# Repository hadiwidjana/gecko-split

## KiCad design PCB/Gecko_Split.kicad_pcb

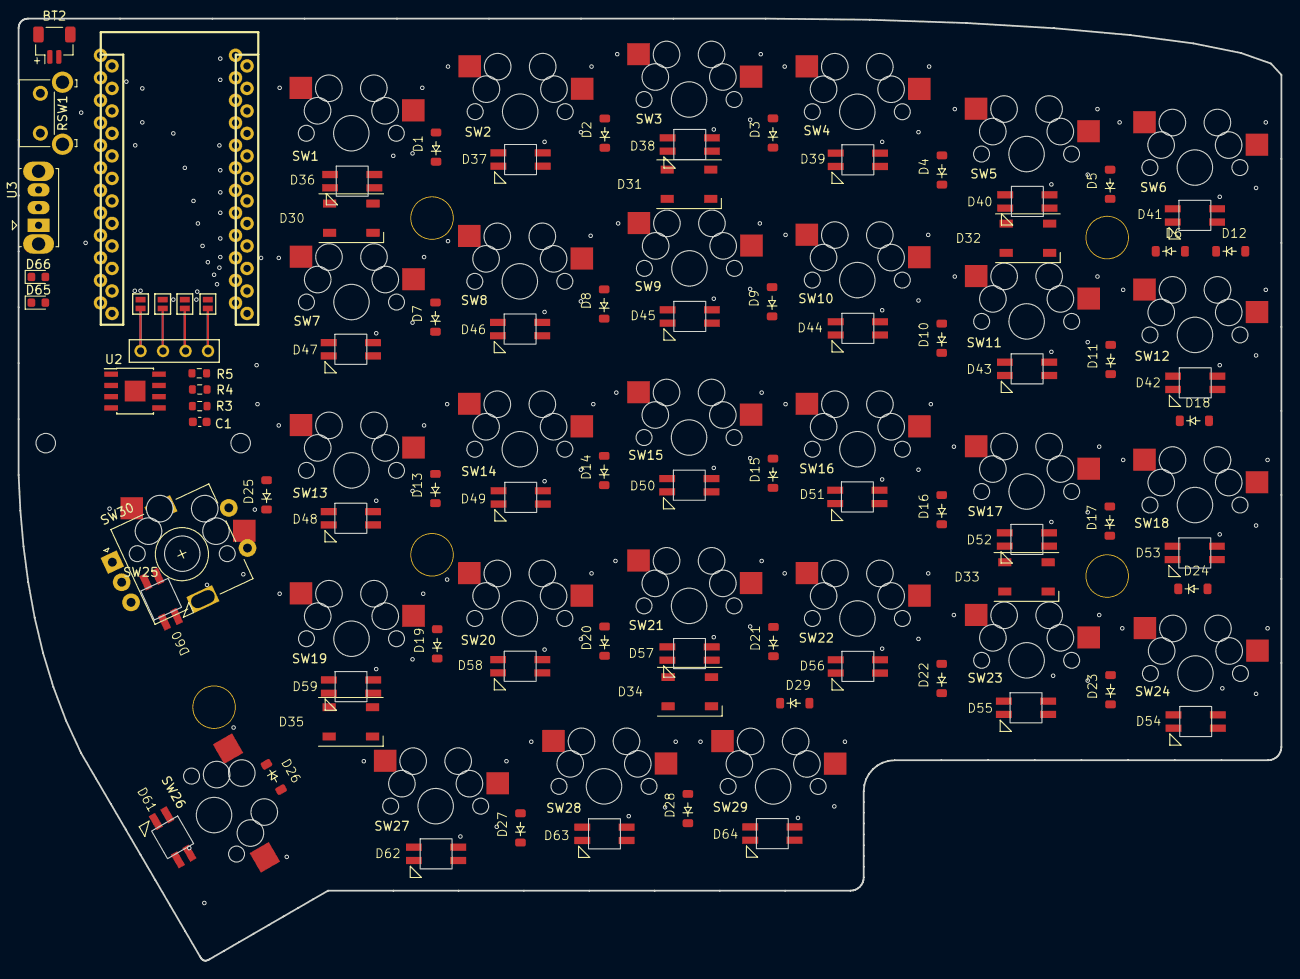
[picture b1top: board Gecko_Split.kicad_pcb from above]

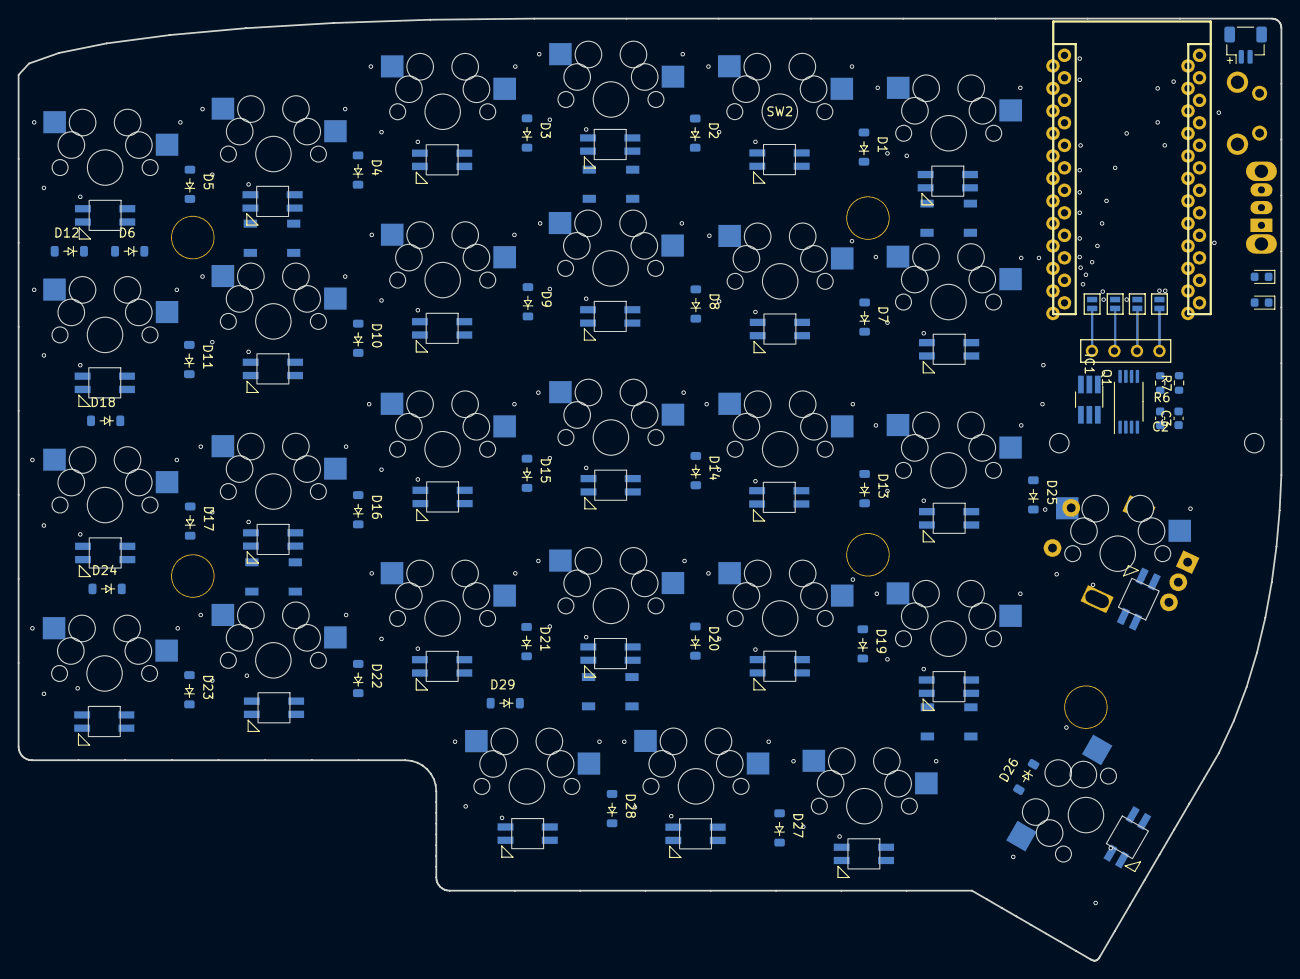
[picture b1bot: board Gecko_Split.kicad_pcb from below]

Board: 2 copper layers, 142.5 x 106.3 mm, 127 parts (10 on the bottom side), 98 nets.

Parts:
BT2: Battery_Cell; JST_SH_BM02B-SRSS-TB_1x02-1MP_P1.00mm_Vertical
C1, C2: 0.1UF-25V-5%; C_0603_1608Metric
C3: 10UF; C_0603_1608Metric
D1, D2, D3, D4, D5, D6, D7, D8, D9, D10, D11, D12, D13, D14, D15, D16, D17, D18, D19, D20, D21, D22, D23, D24, D25, D26, D27, D28, D29: D; D_SOD-123-BothSides
D30, D31, D32, D33, D34, D35: WS2812B; LED_WS2812B_BothSides
D36, D37, D38, D39, D40, D41, D42, D43, D44, D45, D46, D47, D48, D49, D50, D51, D52, D53, D54, D55, D56, D57, D58, D59, D60, D61, D62, D63, D64: SK6812MINI; LED_SK6812MINI_THROUGH
D65, D66: LED; LED_0603_1608Metric
IC1: DW01A; TSOT-23-6_HandSoldering
J2: OLED; OLED_4Pin
JP1, JP2, JP3, JP4, JP5, JP6, JP7, JP8: Jumper_NO_Small; Jumper
Q1: FS8205A; TSSOP-8_4.4x3mm_P0.65mm
R3, R4, R7: 1K OHM; R_0603_1608Metric
R5: 1.2K Ohm; R_0603_1608Metric
R6: 100 OHM; R_0603_1608Metric
RSW1: SW_RST; SW_SPST_Omron_B3F-315x_Angled
SW1, SW2, SW3, SW4, SW5, SW6, SW7, SW8, SW9, SW10, SW11, SW12, SW13, SW14, SW15, SW16, SW17, SW18, SW19, SW20, SW21, SW22, SW23, SW24, SW25, SW26, SW27, SW28, SW29: SW_PUSH; MX_Socket_18mm
SW30: RotaryEncoder_Switch; RotaryEncoder_Alps_EC11E-Switch_Vertical_H20mm
TH1, TH2: HOLE; HOLE_M2
TH3, TH4, TH5, TH6, TH7: HOLE; HOLE_M2_TH
U1: ProMicro; ProMicro_rev2
U2: TP4056; TP4056_SOIC-8
U3: SK12D07VG4; SW_Slide_1P2T_CK_OS102011MS2Q

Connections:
BAT+: C3.1, R6.1, U1.24 (RAW), U2.5 (BAT), U3.1
BAT-: C2.2, IC1.6 (GND), Q1.6, Q1.7
GND: BT2.2 (-), C1.2, C3.2, D30.3 (VSS), D31.3 (VSS), D32.3 (VSS), D33.3 (VSS), D34.3 (VSS), D35.3 (VSS), D36.2 (VSS), D37.2 (VSS), D38.2 (VSS), D39.2 (VSS), D40.2 (VSS), D41.2 (VSS), D42.2 (VSS), D43.2 (VSS), D44.2 (VSS), D45.2 (VSS), D46.2 (VSS), D47.2 (VSS), D48.2 (VSS), D49.2 (VSS), D50.2 (VSS), D51.2 (VSS), D52.2 (VSS), D53.2 (VSS), D54.2 (VSS), D55.2 (VSS), D56.2 (VSS), D57.2 (VSS), D58.2 (VSS), D59.2 (VSS), D60.2 (VSS), D61.2 (VSS), D62.2 (VSS), D63.2 (VSS), D64.2 (VSS), JP1.2, JP8.2, Q1.2, Q1.3, R5.2, R7.2, RSW1.1, SW30.C, U1.3 (GND), U1.4 (GND), U1.23 (GND), U2.1 (TEMP), U2.3 (GND)
LED: D30.4 (DIN), U1.1 (TX(PD3))
unnamed: BT2.1 (+), U3.3
unnamed: D1.2 (A), SW1.2
unnamed: D2.2 (A), SW2.2
unnamed: D3.2 (A), SW3.2
unnamed: D4.2 (A), SW4.2
unnamed: D5.2 (A), SW5.2
unnamed: D6.2 (A), SW6.2
unnamed: D7.2 (A), SW7.2
unnamed: D8.2 (A), SW8.2
unnamed: D9.2 (A), SW9.2
unnamed: D10.2 (A), SW10.2
unnamed: D11.2 (A), SW11.2
unnamed: D12.2 (A), SW12.2
unnamed: D13.2 (A), SW13.2
unnamed: D14.2 (A), SW14.2
unnamed: D15.2 (A), SW15.2
unnamed: D16.2 (A), SW16.2
unnamed: D17.2 (A), SW17.2
unnamed: D18.2 (A), SW18.2
unnamed: D19.2 (A), SW19.2
unnamed: D20.2 (A), SW20.2
unnamed: D21.2 (A), SW21.2
unnamed: D22.2 (A), SW22.2
unnamed: D23.2 (A), SW23.2
unnamed: D24.2 (A), SW24.2
unnamed: D25.2 (A), SW25.2, SW30.S2
unnamed: D26.2 (A), SW26.2
unnamed: D27.2 (A), SW27.2
unnamed: D28.2 (A), SW28.2
unnamed: D29.2 (A), SW29.2
unnamed: D30.2 (DOUT), D31.4 (DIN)
unnamed: D31.2 (DOUT), D32.4 (DIN)
unnamed: D32.2 (DOUT), D33.4 (DIN)
unnamed: D33.2 (DOUT), D34.4 (DIN)
unnamed: D34.2 (DOUT), D35.4 (DIN)
unnamed: D35.2 (DOUT), D36.3 (DIN)
unnamed: D36.1 (DOUT), D37.3 (DIN)
unnamed: D37.1 (DOUT), D38.3 (DIN)
unnamed: D38.1 (DOUT), D39.3 (DIN)
unnamed: D39.1 (DOUT), D40.3 (DIN)
unnamed: D40.1 (DOUT), D41.3 (DIN)
unnamed: D41.1 (DOUT), D42.3 (DIN)
unnamed: D42.1 (DOUT), D43.3 (DIN)
unnamed: D43.1 (DOUT), D44.3 (DIN)
unnamed: D44.1 (DOUT), D45.3 (DIN)
unnamed: D45.1 (DOUT), D46.3 (DIN)
unnamed: D46.1 (DOUT), D47.3 (DIN)
unnamed: D47.1 (DOUT), D48.3 (DIN)
unnamed: D48.1 (DOUT), D49.3 (DIN)
unnamed: D49.1 (DOUT), D50.3 (DIN)
unnamed: D50.1 (DOUT), D51.3 (DIN)
unnamed: D51.1 (DOUT), D52.3 (DIN)
unnamed: D52.1 (DOUT), D53.3 (DIN)
unnamed: D53.1 (DOUT), D54.3 (DIN)
unnamed: D54.1 (DOUT), D55.3 (DIN)
unnamed: D55.1 (DOUT), D56.3 (DIN)
unnamed: D56.1 (DOUT), D57.3 (DIN)
unnamed: D57.1 (DOUT), D58.3 (DIN)
unnamed: D58.1 (DOUT), D59.3 (DIN)
unnamed: D59.1 (DOUT), D60.3 (DIN)
unnamed: D60.1 (DOUT), D61.3 (DIN)
unnamed: D61.1 (DOUT), D62.3 (DIN)
unnamed: D62.1 (DOUT), D63.3 (DIN)
unnamed: D63.1 (DOUT), D64.3 (DIN)
unnamed: D65.1 (K), R4.2
unnamed: D66.1 (K), R3.2
unnamed: IC1.2 (CS), R7.1
unnamed: IC1.3 (OC), Q1.4
unnamed: IC1.1 (OD), Q1.5
unnamed: C2.1, IC1.5 (VCC), R6.2
unnamed: J2.1, JP4.1, JP8.1
unnamed: J2.2, JP3.1, JP7.1
unnamed: J2.3, JP2.1, JP6.1
unnamed: J2.4, JP1.1, JP5.1
unnamed: R5.1, U2.2 (PROG)
unnamed: R4.1, U2.7 (~CHRG)
unnamed: R3.1, U2.6 (~STDBY)
PADA: SW30.A, U1.20 (A3(PF4))
PADB: SW30.B, U1.19 (A2(PF5))
RESET: RSW1.2, U1.22 (RST)
SCL: JP3.2, JP6.2, U1.6 (SCL(PD0))
SDA: JP4.2, JP5.2, U1.5 (SDA(PD1))
VCC: C1.1, D30.1 (VDD), D31.1 (VDD), D32.1 (VDD), D33.1 (VDD), D34.1 (VDD), D35.1 (VDD), D36.4 (VDD), D37.4 (VDD), D38.4 (VDD), D39.4 (VDD), D40.4 (VDD), D41.4 (VDD), D42.4 (VDD), D43.4 (VDD), D44.4 (VDD), D45.4 (VDD), D46.4 (VDD), D47.4 (VDD), D48.4 (VDD), D49.4 (VDD), D50.4 (VDD), D51.4 (VDD), D52.4 (VDD), D53.4 (VDD), D54.4 (VDD), D55.4 (VDD), D56.4 (VDD), D57.4 (VDD), D58.4 (VDD), D59.4 (VDD), D60.4 (VDD), D61.4 (VDD), D62.4 (VDD), D63.4 (VDD), D64.4 (VDD), D65.2 (A), D66.2 (A), JP2.2, JP7.2, U1.21 (VCC), U2.4 (VCC), U2.8 (CE)
col0: SW6.1, SW12.1, SW18.1, SW24.1, U1.18 (A1(PF6))
col1: SW5.1, SW11.1, SW17.1, SW23.1, SW29.1, U1.17 (A0(PF7))
col2: SW4.1, SW10.1, SW16.1, SW22.1, SW28.1, U1.16 (D15(PB1))
col3: SW3.1, SW9.1, SW15.1, SW21.1, SW27.1, U1.15 (D14(PB3))
col4: SW2.1, SW8.1, SW14.1, SW20.1, SW26.1, U1.14 (D16(PB2))
col5: SW1.1, SW7.1, SW13.1, SW19.1, SW25.1, SW30.S1, U1.13 (D10(PB6))
row0: D1.1 (K), D2.1 (K), D3.1 (K), D4.1 (K), D5.1 (K), D6.1 (K), U1.8 (D5(PC6))
row1: D7.1 (K), D8.1 (K), D9.1 (K), D10.1 (K), D11.1 (K), D12.1 (K), U1.9 (D6(PD7))
row2: D13.1 (K), D14.1 (K), D15.1 (K), D16.1 (K), D17.1 (K), D18.1 (K), U1.10 (D7(PE6))
row3: D19.1 (K), D20.1 (K), D21.1 (K), D22.1 (K), D23.1 (K), D24.1 (K), U1.11 (D8(PB4))
row4: D25.1 (K), D26.1 (K), D27.1 (K), D28.1 (K), D29.1 (K), U1.12 (D9(PB5))

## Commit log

2023-03-23 reroute tracks
2023-03-26 add charging protection, LED and rotary encoder
